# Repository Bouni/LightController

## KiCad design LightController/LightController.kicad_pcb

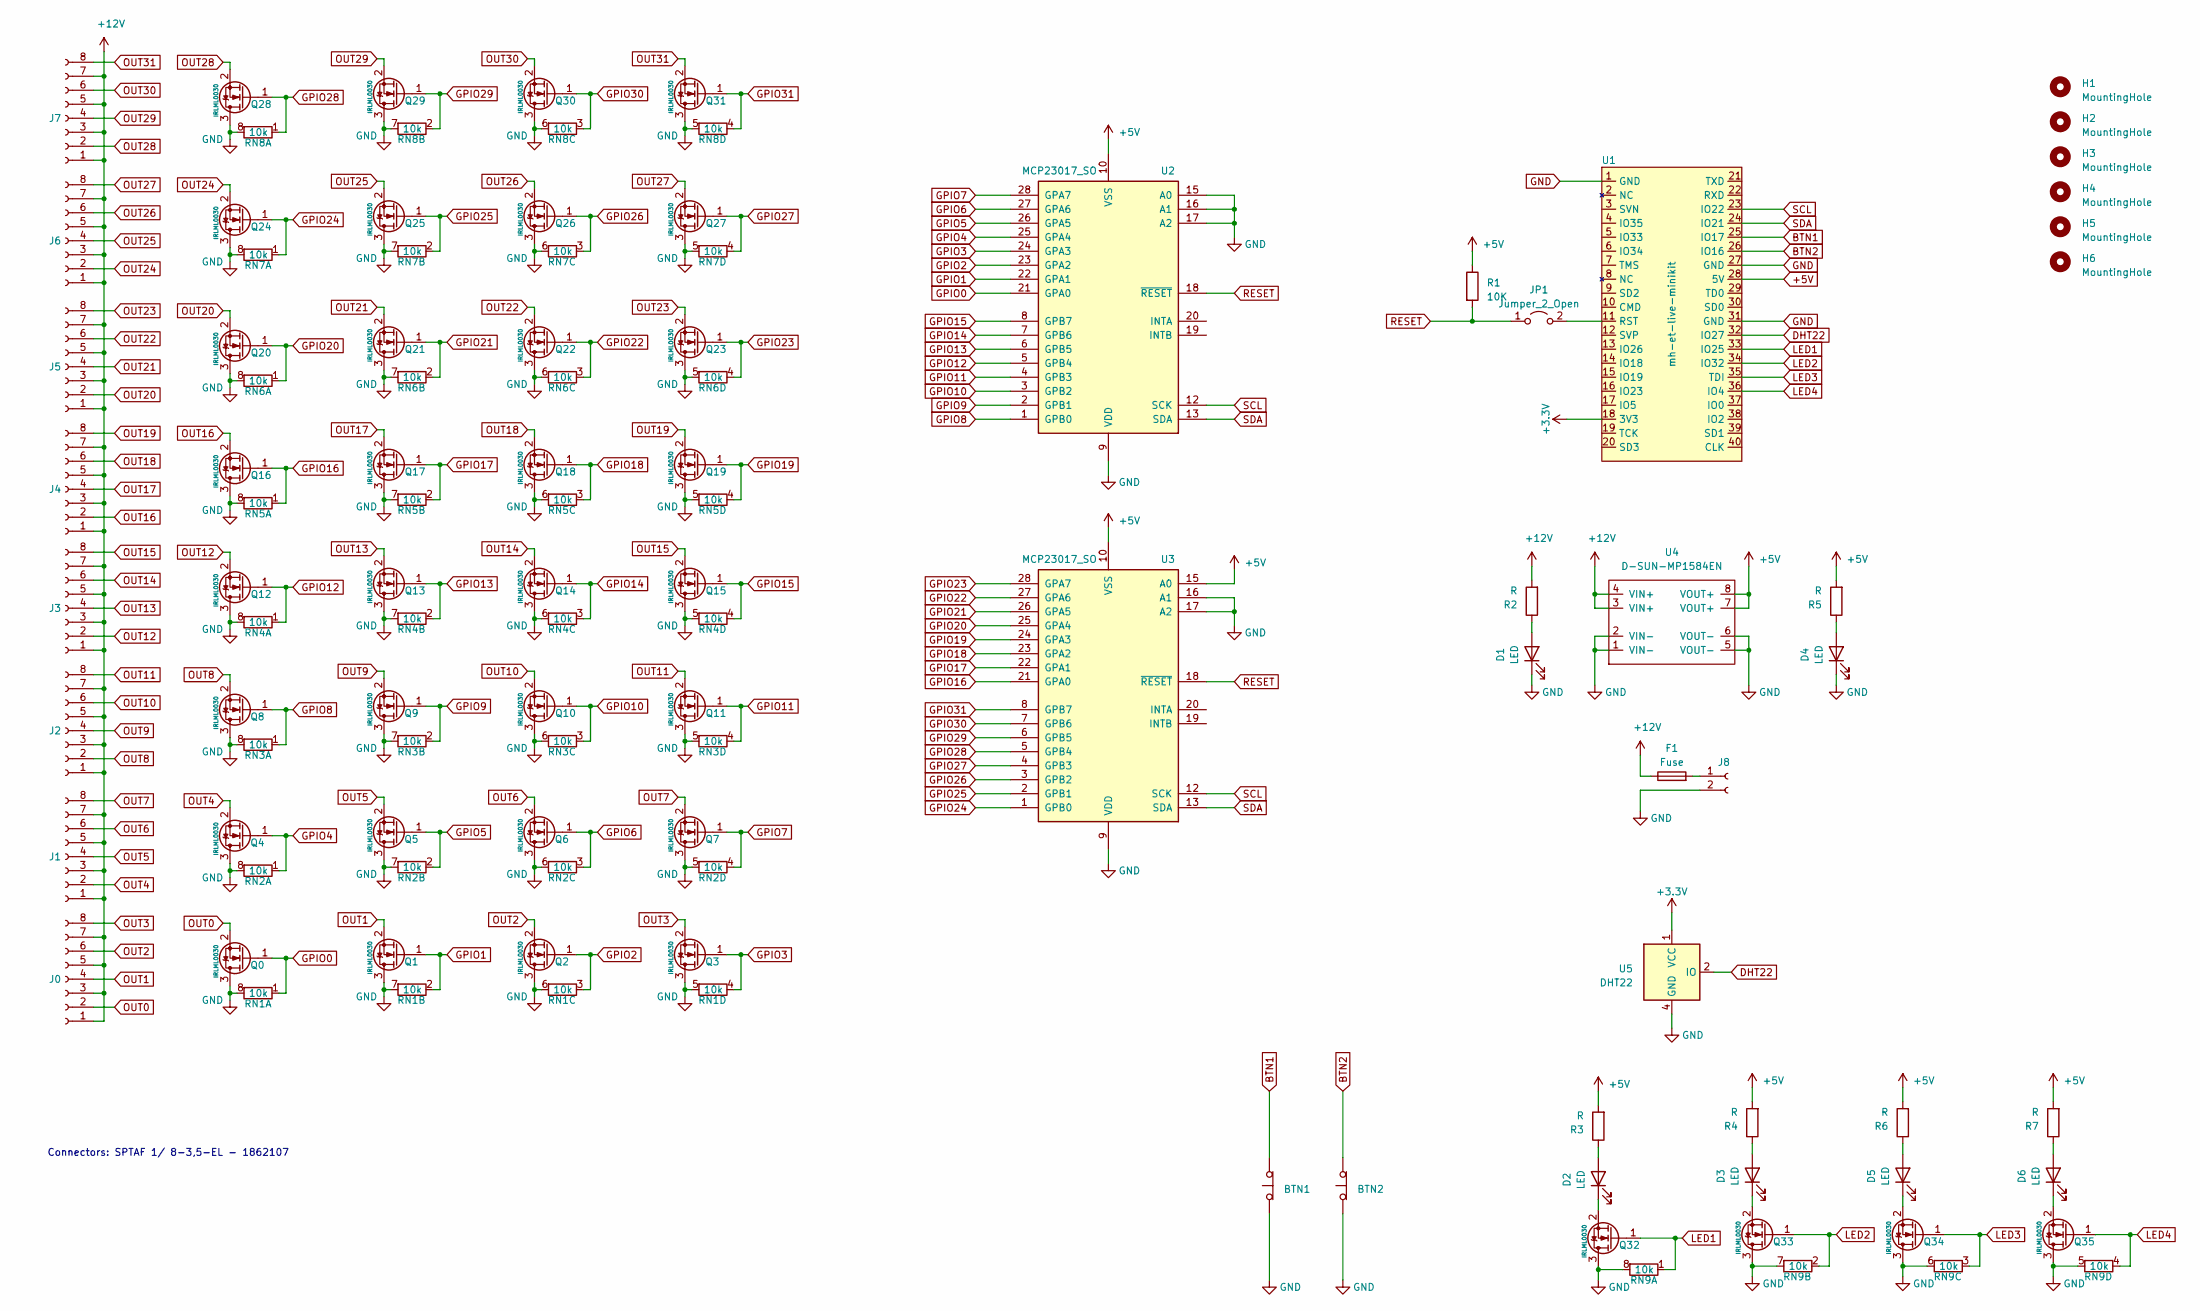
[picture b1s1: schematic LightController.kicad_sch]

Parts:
BTN1, BTN2: SW_Push_Open; SW_SPST_Omron_B3FS-101xP
D1, D2, D3, D4, D5, D6: LED; LED_0603_1608Metric
F1: Fuse; Fuseholder_Cylinder-5x20mm_Schurter_0031_8201_Horizontal_Op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
H1, H2, H3, H4, H5, H6: MountingHole; MountingHole_3.2mm_M3
J0, J1, J2, J3, J4, J5, J6, J7: Conn_01x08_Female; SPTAF_1_8_3_5_EL
J8: Conn_01x02_Female; SPTAF_1_2_3_5_EL
JP1: Jumper_2_Open; SolderJumper-2_P1.3mm_Open_RoundedPad1.0x1.5mm
Q0, Q1, Q2, Q3, Q4, Q5, Q6, Q7, Q8, Q9, Q10, Q11, Q12, Q13, Q14, Q15, Q16, Q17, Q18, Q19, Q20, Q21, Q22, Q23, Q24, Q25, Q26, Q27, Q28, Q29, Q30, Q31, Q32, Q33, Q34, Q35: IRLML0030; SOT-23
R1: 10K; R_0603_1608Metric
R2, R3, R4, R5, R6, R7: R; R_0603_1608Metric
RN1, RN2, RN3, RN4, RN5, RN6, RN7, RN8, RN9: 10k; R_Array_Concave_4x0603
U1: mh-et-live-minikit; MH-ET LIVE MiniKit
U2, U3: MCP23017_SO; SSOP-28_5.3x10.2mm_P0.65mm
U4: D-SUN-MP1584EN
U5: DHT22; Aosong_DHT11_5.5x12.0_P2.54mm

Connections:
+3V3: U1.18 (3V3), U5.1 (VCC)
+5V: R1.1, R3.2, R4.2, R5.2, R6.2, R7.2, U1.28 (5V), U2.10 (VSS), U3.10 (VSS), U3.15 (A0), U4.7 (VOUT+), U4.8 (VOUT+)
+12V: F1.1, J0.1, J0.3, J0.5, J0.7, J1.1, J1.3, J1.5, J1.7, J2.1, J2.3, J2.5, J2.7, J3.1, J3.3, J3.5, J3.7, J4.1, J4.3, J4.5, J4.7, J5.1, J5.3, J5.5, J5.7, J6.1, J6.3, J6.5, J6.7, J7.1, J7.3, J7.5, J7.7, R2.2, U4.3 (VIN+), U4.4 (VIN+)
BTN1: BTN1.2 (B), U1.25 (IO17)
BTN2: BTN2.2 (B), U1.26 (IO16)
DHT22: U1.32 (IO27), U5.2 (IO)
GND: BTN1.1 (A), BTN2.1 (A), D1.1 (K), D4.1 (K), J8.2, Q0.3 (D), Q1.3 (D), Q2.3 (D), Q3.3 (D), Q4.3 (D), Q5.3 (D), Q6.3 (D), Q7.3 (D), Q8.3 (D), Q9.3 (D), Q10.3 (D), Q11.3 (D), Q12.3 (D), Q13.3 (D), Q14.3 (D), Q15.3 (D), Q16.3 (D), Q17.3 (D), Q18.3 (D), Q19.3 (D), Q20.3 (D), Q21.3 (D), Q22.3 (D), Q23.3 (D), Q24.3 (D), Q25.3 (D), Q26.3 (D), Q27.3 (D), Q28.3 (D), Q29.3 (D), Q30.3 (D), Q31.3 (D), Q32.3 (D), Q33.3 (D), Q34.3 (D), Q35.3 (D), RN1.5 (R4.2), RN1.6 (R3.2), RN1.7 (R2.2), RN1.8 (R1.2), RN2.5 (R4.2), RN2.6 (R3.2), RN2.7 (R2.2), RN2.8 (R1.2), RN3.5 (R4.2), RN3.6 (R3.2), RN3.7 (R2.2), RN3.8 (R1.2), RN4.5 (R4.2), RN4.6 (R3.2), RN4.7 (R2.2), RN4.8 (R1.2), RN5.5 (R4.2), RN5.6 (R3.2), RN5.7 (R2.2), RN5.8 (R1.2), RN6.5 (R4.2), RN6.6 (R3.2), RN6.7 (R2.2), RN6.8 (R1.2), RN7.5 (R4.2), RN7.6 (R3.2), RN7.7 (R2.2), RN7.8 (R1.2), RN8.5 (R4.2), RN8.6 (R3.2), RN8.7 (R2.2), RN8.8 (R1.2), RN9.5 (R4.2), RN9.6 (R3.2), RN9.7 (R2.2), RN9.8 (R1.2), U1.1 (GND), U1.27 (GND), U1.31 (GND), U2.9 (VDD), U2.15 (A0), U2.16 (A1), U2.17 (A2), U3.9 (VDD), U3.16 (A1), U3.17 (A2), U4.1 (VIN-), U4.2 (VIN-), U4.5 (VOUT-), U4.6 (VOUT-), U5.4 (GND)
GPIO0: Q0.1 (G), RN1.1 (R1.1), U2.21 (GPA0)
GPIO1: Q1.1 (G), RN1.2 (R2.1), U2.22 (GPA1)
GPIO2: Q2.1 (G), RN1.3 (R3.1), U2.23 (GPA2)
GPIO3: Q3.1 (G), RN1.4 (R4.1), U2.24 (GPA3)
GPIO4: Q4.1 (G), RN2.1 (R1.1), U2.25 (GPA4)
GPIO5: Q5.1 (G), RN2.2 (R2.1), U2.26 (GPA5)
GPIO6: Q6.1 (G), RN2.3 (R3.1), U2.27 (GPA6)
GPIO7: Q7.1 (G), RN2.4 (R4.1), U2.28 (GPA7)
GPIO8: Q8.1 (G), RN3.1 (R1.1), U2.1 (GPB0)
GPIO9: Q9.1 (G), RN3.2 (R2.1), U2.2 (GPB1)
GPIO10: Q10.1 (G), RN3.3 (R3.1), U2.3 (GPB2)
GPIO11: Q11.1 (G), RN3.4 (R4.1), U2.4 (GPB3)
GPIO12: Q12.1 (G), RN4.1 (R1.1), U2.5 (GPB4)
GPIO13: Q13.1 (G), RN4.2 (R2.1), U2.6 (GPB5)
GPIO14: Q14.1 (G), RN4.3 (R3.1), U2.7 (GPB6)
GPIO15: Q15.1 (G), RN4.4 (R4.1), U2.8 (GPB7)
GPIO16: Q16.1 (G), RN5.1 (R1.1), U3.21 (GPA0)
GPIO17: Q17.1 (G), RN5.2 (R2.1), U3.22 (GPA1)
GPIO18: Q18.1 (G), RN5.3 (R3.1), U3.23 (GPA2)
GPIO19: Q19.1 (G), RN5.4 (R4.1), U3.24 (GPA3)
GPIO20: Q20.1 (G), RN6.1 (R1.1), U3.25 (GPA4)
GPIO21: Q21.1 (G), RN6.2 (R2.1), U3.26 (GPA5)
GPIO22: Q22.1 (G), RN6.3 (R3.1), U3.27 (GPA6)
GPIO23: Q23.1 (G), RN6.4 (R4.1), U3.28 (GPA7)
GPIO24: Q24.1 (G), RN7.1 (R1.1), U3.1 (GPB0)
GPIO25: Q25.1 (G), RN7.2 (R2.1), U3.2 (GPB1)
GPIO26: Q26.1 (G), RN7.3 (R3.1), U3.3 (GPB2)
GPIO27: Q27.1 (G), RN7.4 (R4.1), U3.4 (GPB3)
GPIO28: Q28.1 (G), RN8.1 (R1.1), U3.5 (GPB4)
GPIO29: Q29.1 (G), RN8.2 (R2.1), U3.6 (GPB5)
GPIO30: Q30.1 (G), RN8.3 (R3.1), U3.7 (GPB6)
GPIO31: Q31.1 (G), RN8.4 (R4.1), U3.8 (GPB7)
LED1: Q32.1 (G), RN9.1 (R1.1), U1.33 (IO25)
LED2: Q33.1 (G), RN9.2 (R2.1), U1.34 (IO32)
LED3: Q34.1 (G), RN9.3 (R3.1), U1.35 (TDI)
LED4: Q35.1 (G), RN9.4 (R4.1), U1.36 (IO4)
unnamed: D1.2 (A), R2.1
unnamed: D2.1 (K), Q32.2 (S)
unnamed: D2.2 (A), R3.1
unnamed: D3.1 (K), Q33.2 (S)
unnamed: D3.2 (A), R4.1
unnamed: D4.2 (A), R5.1
unnamed: D5.1 (K), Q34.2 (S)
unnamed: D5.2 (A), R6.1
unnamed: D6.1 (K), Q35.2 (S)
unnamed: D6.2 (A), R7.1
unnamed: F1.2, J8.1
unnamed: JP1.2 (B), U1.11 (RST)
OUT0: J0.2, Q0.2 (S)
OUT1: J0.4, Q1.2 (S)
OUT2: J0.6, Q2.2 (S)
OUT3: J0.8, Q3.2 (S)
OUT4: J1.2, Q4.2 (S)
OUT5: J1.4, Q5.2 (S)
OUT6: J1.6, Q6.2 (S)
OUT7: J1.8, Q7.2 (S)
OUT8: J2.2, Q8.2 (S)
OUT9: J2.4, Q9.2 (S)
OUT10: J2.6, Q10.2 (S)
OUT11: J2.8, Q11.2 (S)
OUT12: J3.2, Q12.2 (S)
OUT13: J3.4, Q13.2 (S)
OUT14: J3.6, Q14.2 (S)
OUT15: J3.8, Q15.2 (S)
OUT16: J4.2, Q16.2 (S)
OUT17: J4.4, Q17.2 (S)
OUT18: J4.6, Q18.2 (S)
OUT19: J4.8, Q19.2 (S)
OUT20: J5.2, Q20.2 (S)
OUT21: J5.4, Q21.2 (S)
OUT22: J5.6, Q22.2 (S)
OUT23: J5.8, Q23.2 (S)
OUT24: J6.2, Q24.2 (S)
OUT25: J6.4, Q25.2 (S)
OUT26: J6.6, Q26.2 (S)
OUT27: J6.8, Q27.2 (S)
OUT28: J7.2, Q28.2 (S)
OUT29: J7.4, Q29.2 (S)
OUT30: J7.6, Q30.2 (S)
OUT31: J7.8, Q31.2 (S)
RESET: JP1.1 (A), R1.2, U2.18 (~RESET~), U3.18 (~RESET~)
SCL: U1.23 (IO22), U2.12 (SCK), U3.12 (SCK)
SDA: U1.24 (IO21), U2.13 (SDA), U3.13 (SDA)

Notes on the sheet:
Connectors: SPTAF 1/ 8-3,5-EL - 1862107

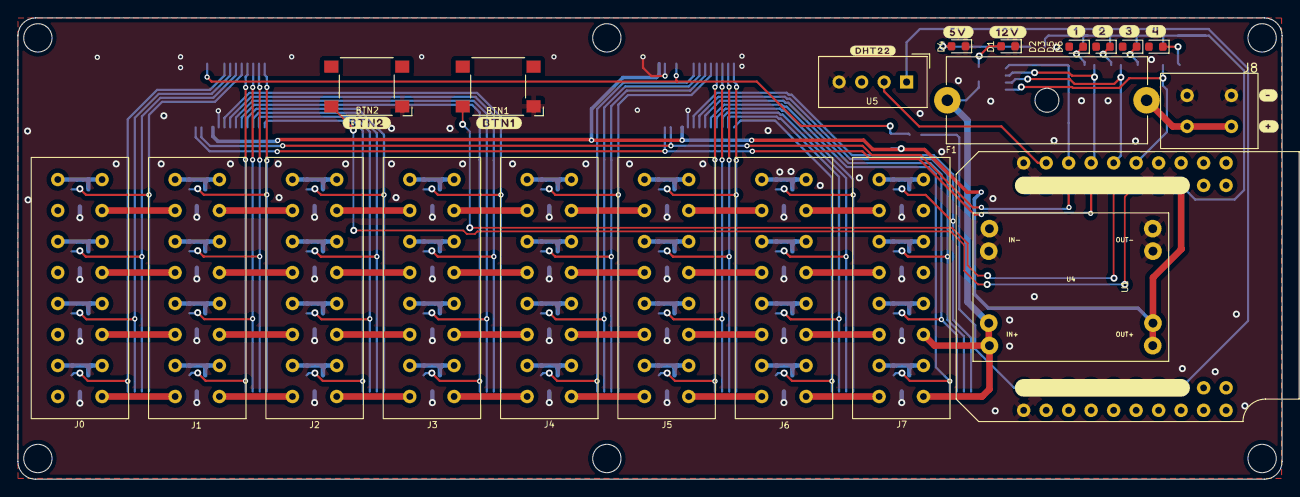
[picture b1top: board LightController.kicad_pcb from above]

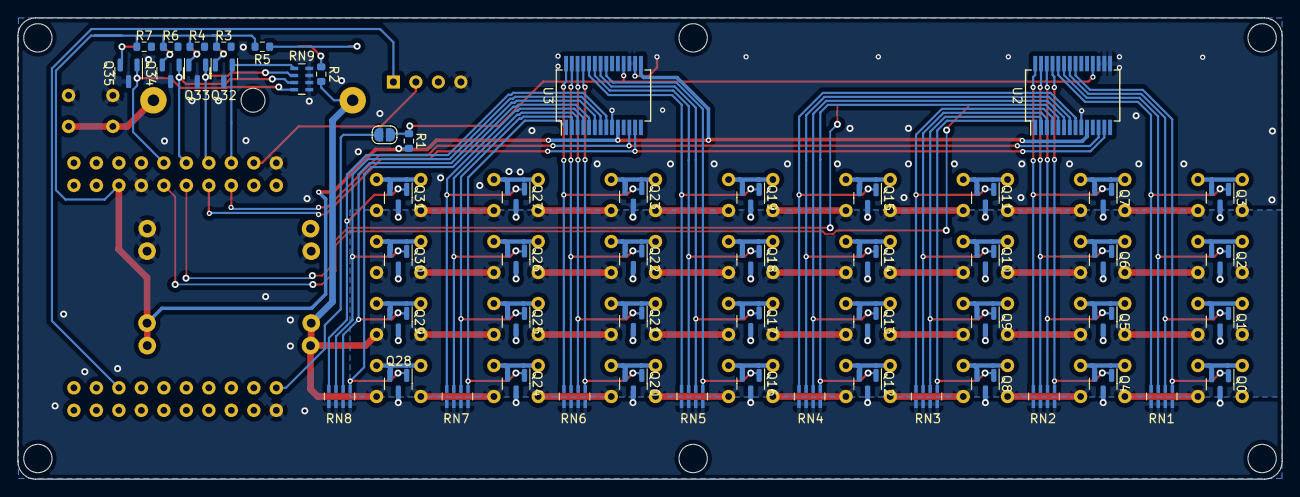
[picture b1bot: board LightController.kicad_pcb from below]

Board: 2 copper layers, 142.8 x 52.1 mm, 82 parts (55 on the bottom side), 90 nets.

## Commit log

2021-04-11 routing almost done
2021-04-11 made pcb slightly bigger for mounting holes
2021-04-11 started positioning labels
